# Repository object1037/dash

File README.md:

# Dash

Environment monitor (Temperature, Relative humidity, CO2) with e-paper display.

Inspired by [pico-env-mon](https://github.com/shapoco/pico-env-mon).

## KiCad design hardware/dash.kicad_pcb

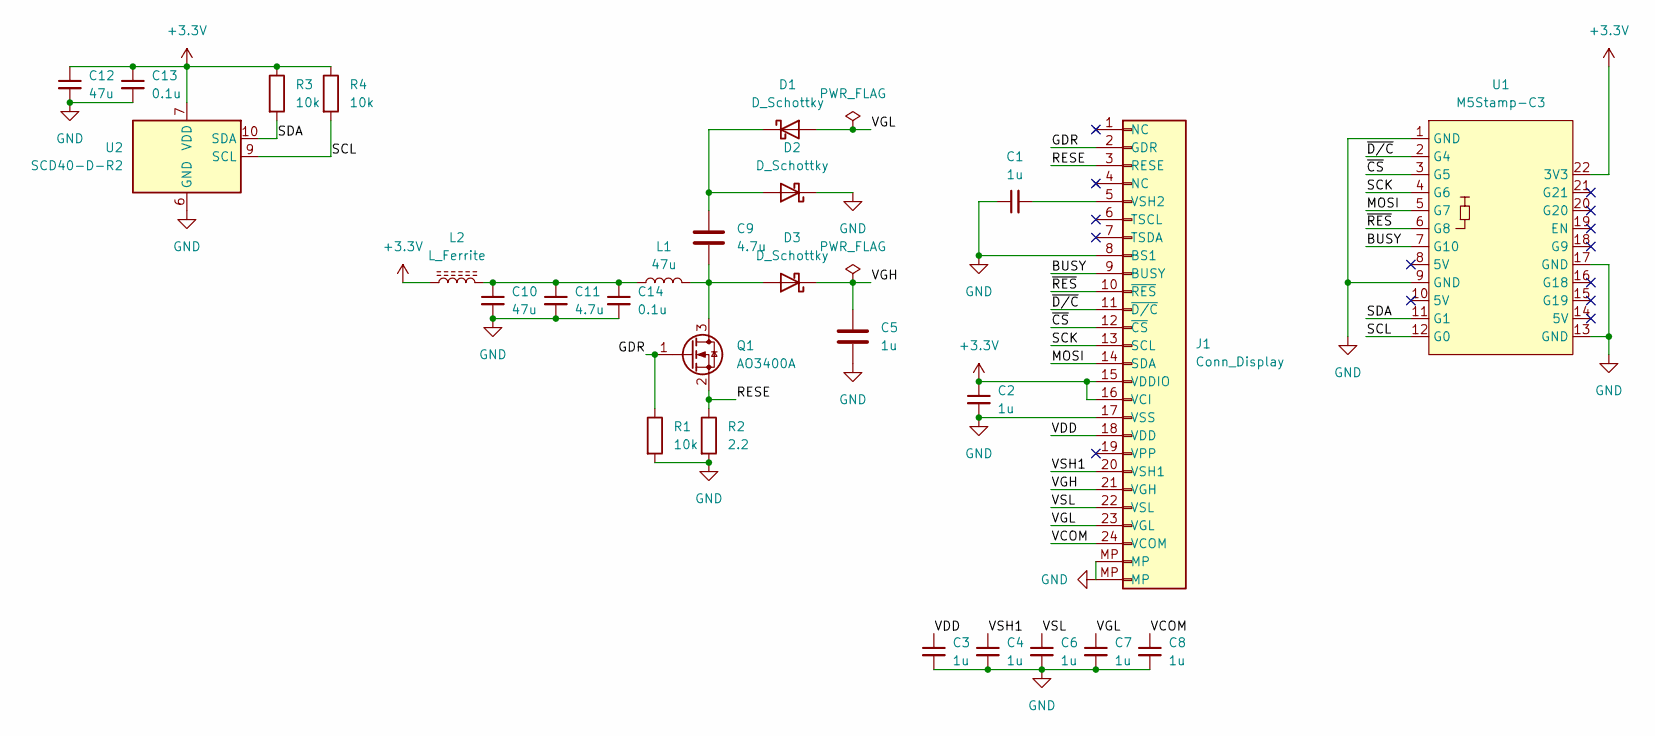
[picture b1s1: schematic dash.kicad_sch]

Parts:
C1, C2, C3, C4, C5, C6, C7, C8: 1u; C_0603_1608Metric_Pad1.08x0.95mm_HandSolder
C9, C11: 4.7u; C_0805_2012Metric_Pad1.18x1.45mm_HandSolder
C10, C12: 47u; C_0805_2012Metric_Pad1.18x1.45mm_HandSolder
C13, C14: 0.1u; C_0603_1608Metric_Pad1.08x0.95mm_HandSolder
D1, D2, D3: D_Schottky; D_SMA
J1: Conn_Display; Jushuo_AFC07-S24FCA-00_1x24-1MP_P0.50_Horizontal
L1: 47u; L_10.4x10.4_H4.8
L2: L_Ferrite; L_0603_1608Metric_Pad1.05x0.95mm_HandSolder
Q1: AO3400A; SOT-23_Handsoldering
R1, R3, R4: 10k; R_0603_1608Metric_Pad0.98x0.95mm_HandSolder
R2: 2.2; R_0603_1608Metric_Pad0.98x0.95mm_HandSolder
U1: M5Stamp-C3; M5Stamp_C3
U2: SCD40-D-R2; Sensirion_SCD4x-1EP_10.1x10.1mm_P1.25mm_EP4.8x4.8mm

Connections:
+3.3V: C2.1, C12.1, C13.1, J1.15 (VDDIO), J1.16 (VCI), L2.1, R3.1, R4.1, U1.22 (3V3), U2.7 (VDD), U2.19 (VDD)
/BUSY: J1.9 (BUSY), U1.7 (G10)
/GDR: J1.2 (GDR), Q1.1 (G), R1.1
/MOSI: J1.14 (SDA), U1.5 (G7)
/RESE: J1.3 (RESE), Q1.2 (S), R2.1
/SCK: J1.13 (SCL), U1.4 (G6)
/SCL: R4.2, U1.12 (G0), U2.9 (SCL)
/SDA: R3.2, U1.11 (G1), U2.10 (SDA)
/VCOM: C8.1, J1.24 (VCOM)
/VDD: C3.1, J1.18 (VDD)
/VGH: C5.1, D3.1 (K), J1.21 (VGH)
/VGL: C7.1, D1.2 (A), J1.23 (VGL)
/VSH1: C4.1, J1.20 (VSH1)
/VSL: C6.1, J1.22 (VSL)
/~CS: J1.12 (~CS), U1.3 (G5)
/~D/C: J1.11 (~D/C), U1.2 (G4)
/~RES: J1.10 (~RES), U1.6 (G8)
GND: C1.1, C2.2, C3.2, C4.2, C5.2, C6.2, C7.2, C8.2, C10.2, C11.2, C12.2, C13.2, C14.2, D2.1 (K), J1.8 (BS1), J1.17 (VSS), J1.MP, R1.2, R2.2, U1.1 (GND), U1.9 (GND), U1.13 (GND), U1.17 (GND), U2.6 (GND), U2.20 (GND), U2.21 (GND)
unnamed: C10.1, C11.1, C14.1, L1.1, L2.2
unnamed: C9.1, D1.1 (K), D2.2 (A)
unnamed: C9.2, D3.2 (A), L1.2, Q1.3 (D)
unnamed: C1.2, J1.5 (VSH2)

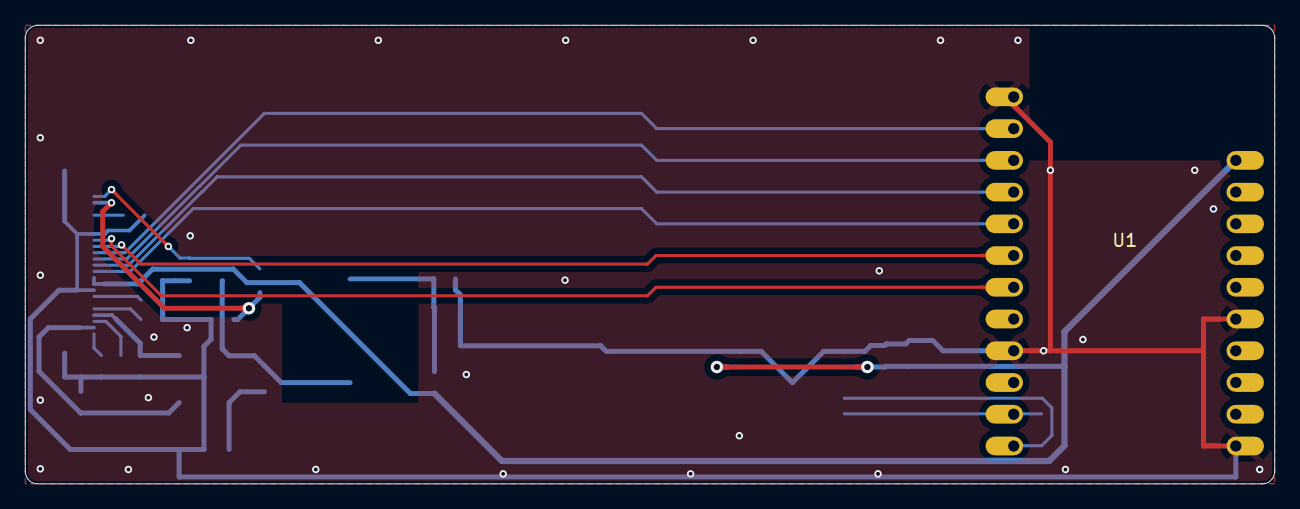
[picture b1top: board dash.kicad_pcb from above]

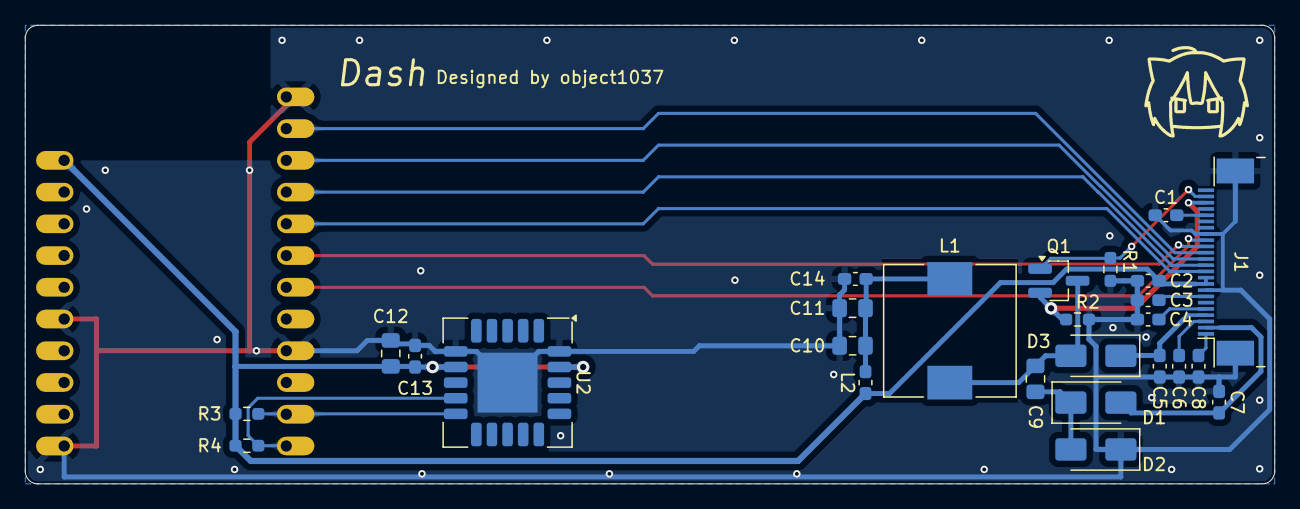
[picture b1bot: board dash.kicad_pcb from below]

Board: 2 copper layers, 100.0 x 36.7 mm, 27 parts (26 on the bottom side), 22 nets.

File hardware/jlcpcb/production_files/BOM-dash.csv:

Comment,Designator,Footprint,LCSC,Quantity
0.1u,"C13,C14",C_0603_1608Metric_Pad1.08x0.95mm_HandSolder,C14663,2
L_Ferrite,L2,L_0603_1608Metric_Pad1.05x0.95mm_HandSolder,C14709,1
1u,"C1,C2,C3,C4,C5,C6,C7,C8",C_0603_1608Metric_Pad1.08x0.95mm_HandSolder,C15849,8
47u,"C10,C12",C_0805_2012Metric_Pad1.18x1.45mm_HandSolder,C16780,2
4.7u,"C11,C9",C_0805_2012Metric_Pad1.18x1.45mm_HandSolder,C1779,2
AO3400A,Q1,SOT-23_Handsoldering,C20917,1
2.2,R2,R_0603_1608Metric_Pad0.98x0.95mm_HandSolder,C22939,1
D_Schottky,"D1,D2,D3",D_SMA,C2480,3
10k,"R1,R3,R4",R_0603_1608Metric_Pad0.98x0.95mm_HandSolder,C25804,3
SCD40-D-R2,U2,Sensirion_SCD4x-1EP_10.1x10.1mm_P1.25mm_EP4.8x4.8mm,C3037696,1
Conn_Display,J1,Jushuo_AFC07-S24FCA-00_1x24-1MP_P0.50_Horizontal,C5362165,1
47u,L1,L_10.4x10.4_H4.8,C9934,1

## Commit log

2025-08-29 init
2025-08-29 update schema
2025-08-30 schmatic complete
2025-08-30 finish pcb
2025-10-18 init with blink example
2025-10-18 plot schematic
2025-10-18 setup components
2025-11-01 hello world with sensor and display
2025-11-01 add display simulator
2025-11-01 display axis
2025-11-01 basic number display
2025-11-01 add small fonts
2025-11-02 display sensor values
2025-11-02 display graph
2025-11-03 fill graph and bug fix
2025-11-03 add README
2025-11-03 update statistic operation algorithm
2025-11-03 fix filter calculation bug
2025-11-03 use low power measurement for better temp/rh precision
2025-11-03 offset temp by 1deg
2025-11-03 update parameters
2025-11-03 round number and support 0.05 tick
2025-11-04 clamp graph steps to 0--40
2025-11-04 proper handling for large scale
2026-01-07 add serial output for data logging
2026-01-08 add logger program
2026-01-08 update csv location
2026-01-08 externalize env vars
2026-01-08 optimization
2026-01-08 reduce cpu usage
2026-01-08 fix port open handling
2026-04-06 add image for readme
